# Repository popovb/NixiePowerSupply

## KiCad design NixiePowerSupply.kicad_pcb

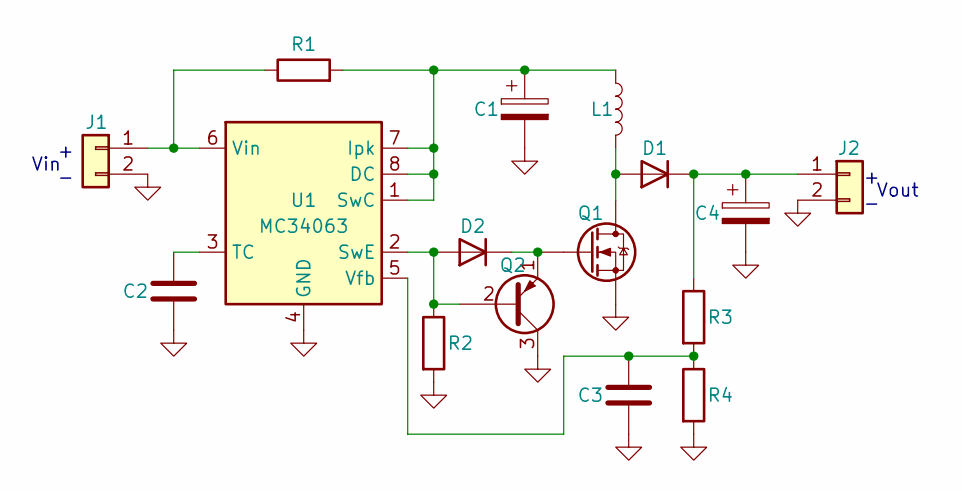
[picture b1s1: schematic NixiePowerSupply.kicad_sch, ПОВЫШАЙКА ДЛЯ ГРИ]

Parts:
C1: 220uF 16V LESR Polar 6.3x2.5; CP_Radial_D6.3mm_P2.50mm
C2: 2200pF, 0805; C_0805_2012Metric_Pad1.18x1.45mm_HandSolder
C3: 0.01uF, 0805; C_0805_2012Metric_Pad1.18x1.45mm_HandSolder
C4: 2.2uF 250V Polar 6.3x2.5; CP_Radial_D6.3mm_P2.50mm
D1: UF4004 UF4007, DO-41; D_DO-41_SOD81_P7.62mm_Horizontal
D2: 1N4148 1N914, DO-35; D_DO-35_SOD27_P7.62mm_Horizontal
J1, J2: DG301-5.0-2P; DG301-5.0-2P-1X
L1: 220uH, 12x12; L_12x12mm_H8mm
Q1: IRF740, TO-220; TO-220-3_Vertical
Q2: MPSA56, TO-92; TO-92_Inline
R1: 0.33, 0805; R_0805_2012Metric_Pad1.20x1.40mm_HandSolder
R2: 1K, 0805; R_0805_2012Metric_Pad1.20x1.40mm_HandSolder
R3: 470K, 1%; R_Axial_DIN0207_L6.3mm_D2.5mm_P7.62mm_Horizontal
R4: 3K, 1%; R_Axial_DIN0207_L6.3mm_D2.5mm_P7.62mm_Horizontal
U1: MC34063; DIP-8_W7.62mm

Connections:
GND: C1.2, C2.2, C3.2, C4.2, J1.2, J2.2, Q1.3 (S), Q2.3 (C), R2.2, R4.2, U1.4 (GND)
unnamed: D1.2 (A), L1.2, Q1.2 (D)
unnamed: C4.1, D1.1 (K), J2.1, R3.1
unnamed: D2.2 (A), Q2.2 (B), R2.1, U1.2 (SwE)
unnamed: D2.1 (K), Q1.1 (G), Q2.1 (E)
unnamed: J1.1, R1.1, U1.6 (Vin)
unnamed: C1.1, L1.1, R1.2, U1.1 (SwC), U1.7 (Ipk), U1.8 (DC)
unnamed: C2.1, U1.3 (TC)
unnamed: C3.1, R3.2, R4.1, U1.5 (Vfb)

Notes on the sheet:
Vin
Vout

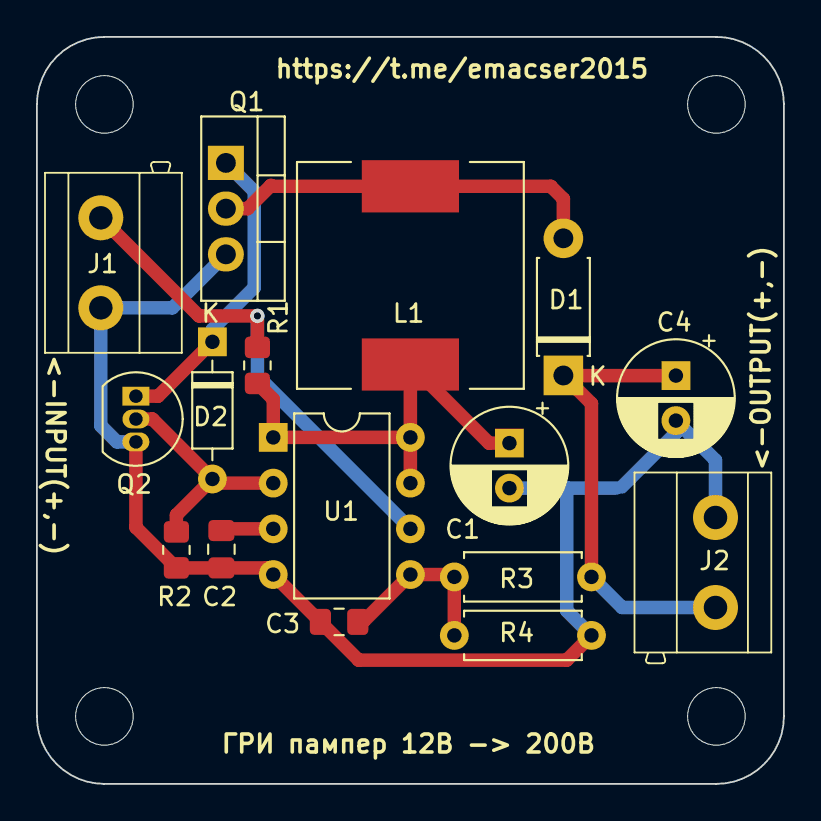
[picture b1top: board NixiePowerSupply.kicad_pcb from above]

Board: 2 copper layers, 41.5 x 41.5 mm, 16 parts (0 on the bottom side), 9 nets.

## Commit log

2024-01-24 init commit
2024-01-30 fix .gitignore
2024-01-30 add Library.pretty
2024-01-30 add footprints
2024-06-02 add pin numbers for Q2
2024-06-02 begin pcb
2024-06-02 first electrical circuit on pcb
2024-06-02 add outline
2024-06-02 fix silk layer
2024-06-02 add filling gnd
2024-06-02 add date to pcb
2024-06-02 mark input, output
2024-06-02 add logos
2024-06-02 add ibom
2024-06-02 fix R3, R4
2024-06-02 add gerbers
2024-06-02 fix links in bom
2024-06-02 add LICENSE
2024-06-02 add pdf for schema
2024-06-02 add pics
